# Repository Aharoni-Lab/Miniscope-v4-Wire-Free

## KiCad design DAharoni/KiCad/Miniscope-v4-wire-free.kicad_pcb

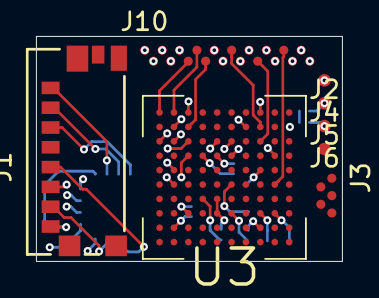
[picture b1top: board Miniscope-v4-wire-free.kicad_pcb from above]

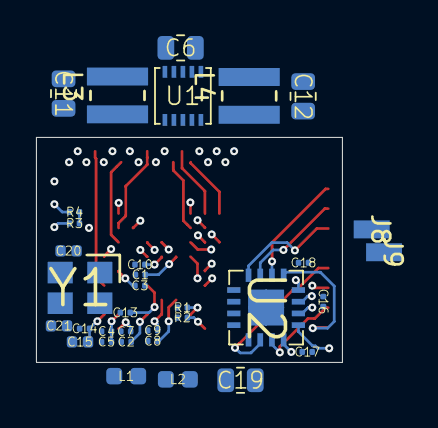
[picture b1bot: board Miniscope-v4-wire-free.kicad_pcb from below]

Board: 6 copper layers, 17.0 x 12.5 mm, 42 parts (34 on the bottom side), 45 nets.

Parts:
C1, C2, C3, C4, C7, C8, C9, C10, C13, C14, C16, C17, C18: GRM033R61A104ME15D; C_0201_0603Metric_L
C5: GRM033R60J105MEA2D; C_0201_0603Metric_L
C6: GRM21BR61E106MA73L; C_0805_2012Metric_L
C11, C12: GRM21BR61C226ME44L; C_0805_2012Metric_L
C15: GRM155R60J475ME87D; C_0402_1005Metric_L
C19: 47uF; C_0805_2012Metric_L
C20, C21: GRM1555C1H120JA01D; C_0402_1005Metric_L
J1: 0475710001
J2, J4, J5, J6: Conn_01x01; Conn_1x1_700_Circular_Pad
J3: Conn_01x05; B2B_Flex_05_Dual_Row_38milx24mil_Pad_20mil_copy
J8, J9: Conn_01x01; Conn_1x1_250x750_Pad
J10: Conn_01x20; B2B_Flex_20_Dual_Row_38milx24mil_Pad_20mil
L1, L2: BLM18PG471SN1D; L_0603_1608Metric_L
L3, L4: VLS3012HBX-2R2M
R1, R2: 10K; R_0201_0603Metric_ERJ_L
R3, R4: 100K; R_0201_0603Metric_ERJ_L
U1: TPS62402-Q1; SON_10_P50_300X300X100L40X24L
U2: MAX13030EETE+; QFN_17_P65_400X400X80L50X30T210L
U3: ATSAME70N21A-CN; BGA_100_CP80_10X10_900X900X110B40L
Y1: ABM8G-12.000MHZ-4Y-T3; OSCCC320X250X100L80X100

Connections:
+1V2: C4.1, C5.1, C9.1, C10.1, L1.1, L2.1, U3.C3, U3.C6, U3.D6, U3.G6
+1V8: C1.1, C2.1, C3.1, C11.1, C13.1, C14.1, C15.1, C16.1, J2.1, J10.15, L3.2, R1.1, R2.1, R3.1, R4.1, U1.4, U2.2, U2.11, U3.C2, U3.C5, U3.E5, U3.E6, U3.F3, U3.G7
+3V3: C12.1, C17.1, C18.1, C19.2, J1.P4, J3.5, J10.1, L4.2, U1.1, U2.16
+BATT: C6.1, J8.1, U1.3, U1.5, U1.7, U1.9
/D0: J10.13, U3.F9
/D1: J10.12, U3.H10
/D2: J10.10, U3.H9
/D3: J10.9, U3.J9
/D4: J10.7, U3.K9
/D5: J10.8, U3.J8
/D6: J10.6, U3.K10
/D7: J10.5, U3.G5
/FV: J10.4, U3.H6
/LED_ENT: J3.1, U3.F8
/LV: J10.3, U3.J1
/MISO: J10.19, U3.K3
/MONITOR0: J10.18, U3.G2
/MOSI: J10.20, U3.H5
/PXL_CLK: J10.11, U3.J3
/RESET_N: J10.17, U3.E2
/SCK: J10.16, U3.J4
/SCL: J3.2, R1.2, U3.C8
/SD0: U2.1, U3.C7
/SD1: U2.3, U3.A7
/SD2: U2.4, U3.K8
/SD3: U2.9, U3.H8
/SDA: J3.3, R2.2, U3.B9
/SDCLKA: U2.12, U3.H7
/SDCMDA: U2.10, U3.A9
/SS_N: J10.14, U3.H3
/SWDCLK: J5.1, R3.2, U3.E9
/SWDIO: J4.1, R4.2, U3.G8
/VDDPLL: C8.1, L2.2, U3.D7
/VDDUTMIC: C7.1, L1.2, U3.B3
/XIN: C20.2, U3.A1, Y1.1
/XOUT: C21.2, U3.A2, Y1.3
GND: C1.2, C2.2, C3.2, C4.2, C5.2, C6.2, C7.2, C8.2, C9.2, C10.2, C11.2, C12.2, C13.2, C14.2, C15.2, C16.2, C17.2, C18.2, C19.1, C20.1, C21.1, J1.G1, J1.G2, J1.G3, J1.P6, J3.4, J6.1, J9.1, J10.2, U1.2, U1.8, U2.13, U2.17, U3.A8, U3.C4, U3.D4, U3.E4, U3.E7, U3.F4, U3.F5, U3.F6, Y1.2, Y1.4
unnamed: J1.P1, U2.6
unnamed: J1.P2, U2.7
unnamed: J1.P3, U2.8
unnamed: J1.P5, U2.14
unnamed: J1.P7, U2.15
unnamed: J1.P8, U2.5
unnamed: L3.1, U1.6
unnamed: L4.1, U1.10

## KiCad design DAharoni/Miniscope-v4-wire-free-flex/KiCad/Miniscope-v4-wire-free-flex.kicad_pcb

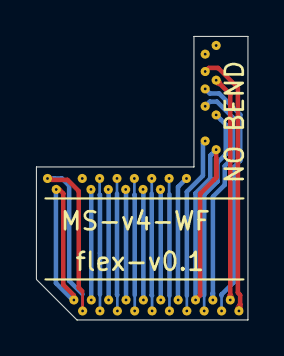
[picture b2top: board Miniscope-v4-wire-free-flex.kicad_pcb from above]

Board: 2 copper layers, 11.8 x 15.8 mm, 3 parts (0 on the bottom side), 23 nets.

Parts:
J1, J3: Conn_01x20; B2B_Flex_20_Dual_Row_38milx24mil_Hole_10milx20mil_small_hole
J2: Conn_01x14; B2B_Flex_14_Dual_Row_38milx24mil_Hole_10milx20mil_small_hole

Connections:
+1V8: J1.2, J2.13, J3.6
+3V3: J1.19, J2.3, J3.20
+5V: J1.18, J2.1
/CLK_OUT: J1.7, J3.10
/DOUT2: J1.4, J3.8
/DOUT3: J1.6, J3.9
/DOUT4: J1.8, J3.11
/DOUT5: J1.9, J3.12
/DOUT6: J1.11, J3.14
/DOUT7: J1.10, J3.13
/DOUT8: J1.12, J3.15
/DOUT9: J1.13, J3.16
/FV: J1.14, J3.17
/I2C_SCL: J1.17, J2.10
/I2C_SDA: J1.16, J2.11
/LV: J1.15, J3.18
/MISO: J2.5, J3.2
/MONITOR0: J2.6, J3.3
/MOSI: J2.4, J3.1
/RESET_N: J2.8, J3.4
/SCK: J2.9, J3.5
/SS_N: J2.12, J3.7
GND: J1.1, J1.20, J2.14, J3.19

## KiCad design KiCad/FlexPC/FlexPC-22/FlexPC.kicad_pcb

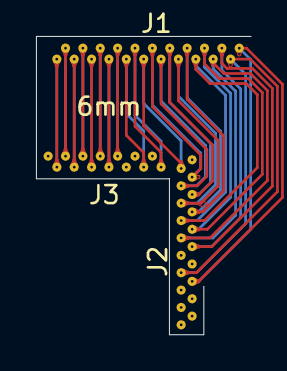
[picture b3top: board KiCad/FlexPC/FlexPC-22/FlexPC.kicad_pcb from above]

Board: 2 copper layers, 11.9 x 16.6 mm, 3 parts (0 on the bottom side), 22 nets.

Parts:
J1: Conn_01x22; B2B_Flex_22_Dual_Row_38milx24mil_Hole_10milx20mil
J2: Conn_01x20; B2B_Flex_20_Dual_Row_38milx24mil_Hole_10milx20mil
J3: Conn_01x14; B2B_Flex_14_Dual_Row_38milx24mil_Hole_10milx20mil

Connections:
/1V8: J1.12, J2.2
/3V3: J1.21, J3.3
/CLK_OUT: J1.7, J2.7
/FRAME_VALID: J1.2, J2.14
/GND: J1.13, J3.14
/LINE_VALID: J1.1, J2.15
/MISO: J1.19, J3.5
/MONITOR0: J1.18, J3.6
/MOSI: J1.20, J3.4
/RESET_N: J1.16, J3.8
/SCK: J1.15, J3.9
/SS_N: J1.14, J3.12
/Status_LED: J1.22, J3.2
/TRIGGER0: J1.17, J3.7
/img_d0: J1.11, J2.3
/img_d1: J1.9, J2.5
/img_d2: J1.10, J2.4
/img_d3: J1.8, J2.6
/img_d4: J1.6, J2.8
/img_d5: J1.5, J2.9
/img_d6: J1.3, J2.11
/img_d7: J1.4, J2.10

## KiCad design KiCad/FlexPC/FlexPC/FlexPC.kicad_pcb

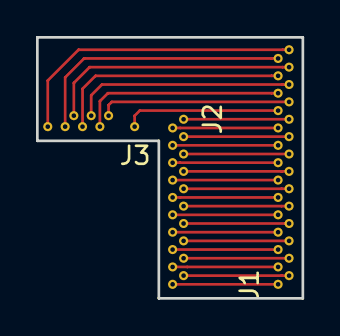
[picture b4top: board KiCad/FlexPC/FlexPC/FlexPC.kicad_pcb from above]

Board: 2 copper layers, 14.8 x 14.5 mm, 3 parts (0 on the bottom side), 28 nets.

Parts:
J1: Conn_01x28; B2B_Flex_28_Dual_Row_38milx24mil_Hole_10milx20mil
J2: Conn_01x20; B2B_Flex_20_Dual_Row_38milx24mil_Hole_10milx20mil
J3: Conn_01x08; B2B_Flex_08_Dual_Row_38milx24mil_Hole_10milx20mil

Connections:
/CLK_OUT: J1.7, J2.14
/FRAME_VALID: J1.14, J2.7
/LINE_VALID: J1.15, J2.6
/MISO: J1.26, J3.6
/MONITOR0: J1.25, J3.5
/MOSI: J1.27, J3.7
/RESET_N: J1.23, J3.3
/SCK: J1.22, J3.2
/SS_N: J1.21, J3.1
/Status_LED: J1.28, J3.8
/TRIGGER0: J1.24, J3.4
/img_d0: J1.3, J2.18
/img_d1: J1.5, J2.16
/img_d2: J1.4, J2.17
/img_d3: J1.6, J2.15
/img_d4: J1.8, J2.13
/img_d5: J1.9, J2.12
/img_d6: J1.11, J2.10
/img_d7: J1.10, J2.11
unnamed: J1.1, J2.20
unnamed: J1.2, J2.19
unnamed: J1.12, J2.9
unnamed: J1.13, J2.8
unnamed: J1.16, J2.5
unnamed: J1.17, J2.4
unnamed: J1.18, J2.3
unnamed: J1.19, J2.2
unnamed: J1.20, J2.1
